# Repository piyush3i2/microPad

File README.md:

# RP2040 6-Key RGB Macro Pad

A compact RP2040-based macro pad with 6 keys, 4 SK6812 Mini RGB LEDs, and an SSD1306 OLED display.  
Built using MicroPython and KMK.

## Overview

This project is a custom USB macro pad.  
Each key sends a keyboard input, lights up an RGB LED, and the OLED shows basic status text.

---

## Hackpad

---

## Schematic

---

## PCB

---

## Case & Assembly

---

## Bill of Materials (BOM)

| Quantity | Component |
|--------:|-----------|
| 4 | SK6812 Mini RGB LED |
| 1 | MCP1700-330MB Voltage Regulator |
| 1 | MCP1700-500MB Voltage Regulator |
| 6 | MX-Style Mechanical Switch |
| 1 | XIAO-nRF52840-SMD |
| 1 | SSD1306 OLED Display |
| 2 | PinSocket 2.54mm 1x04 Vertical |
| 2 | PinHeader 2.54mm 1x02 Horizontal |

---

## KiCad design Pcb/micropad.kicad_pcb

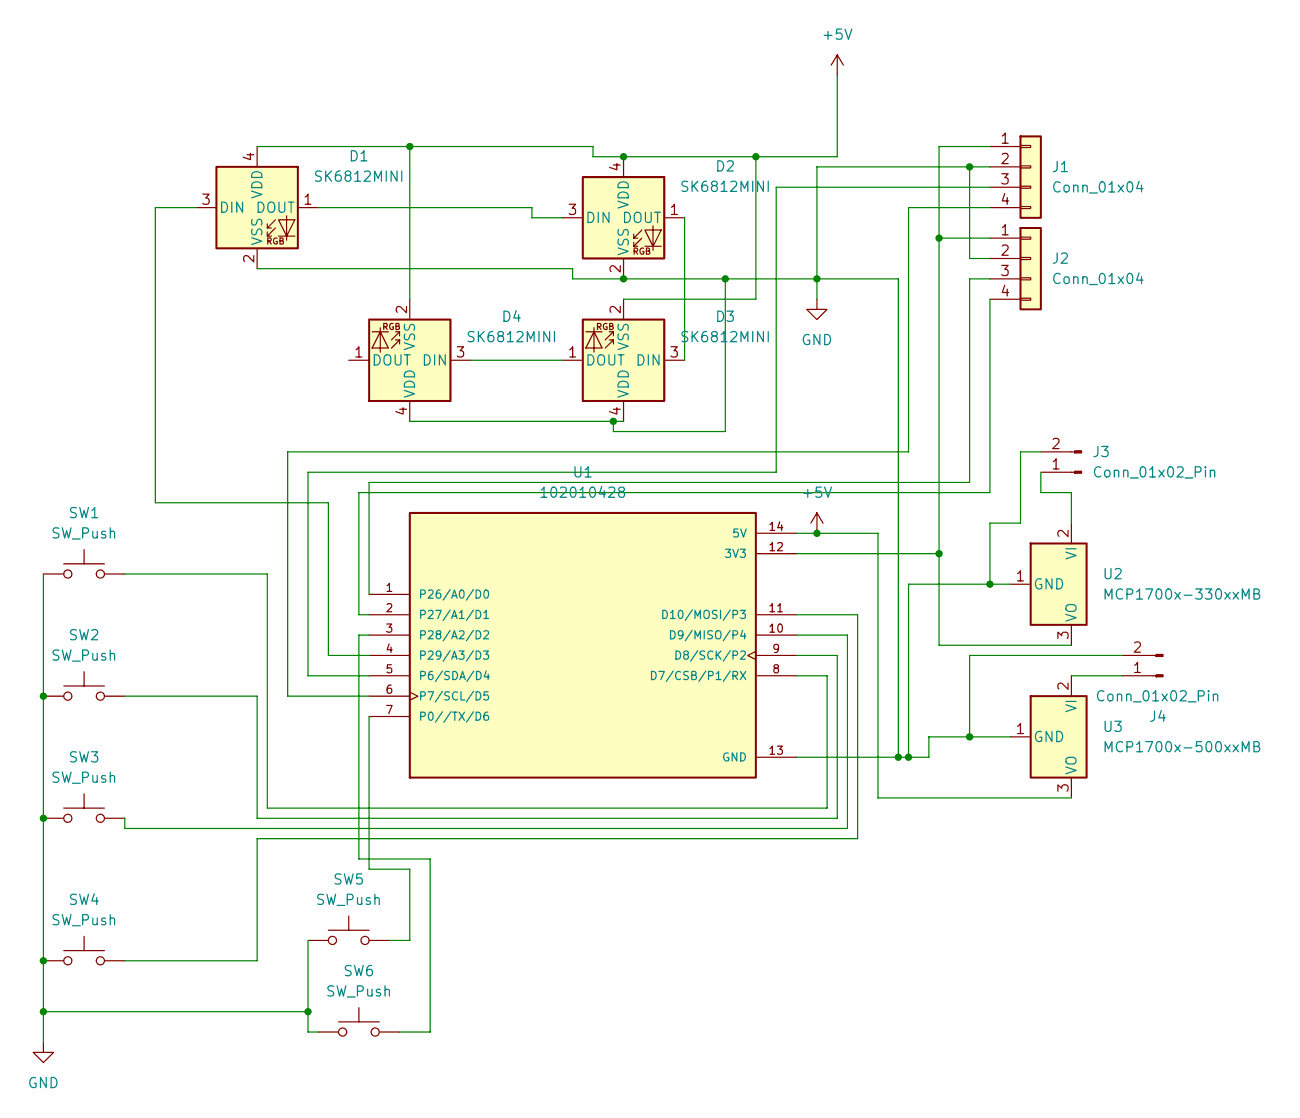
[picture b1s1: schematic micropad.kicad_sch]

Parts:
D1, D2, D3, D4: SK6812MINI; LED_SK6812MINI_PLCC4_3.5x3.5mm_P1.75mm
J1, J2: Conn_01x04; PinSocket_1x04_P2.54mm_Vertical
J3, J4: Conn_01x02_Pin; PinHeader_1x02_P2.54mm_Horizontal
SW1, SW2, SW3, SW4, SW5, SW6: SW_Push; SW_Cherry_MX_1.00u_PCB
U1: 102010428; MODULE_102010428; PARTREV 1.3; DigiKey_Part_Number 1597-102010428-ND
U2: MCP1700x-330xxMB; SOT-89-3
U3: MCP1700x-500xxMB; SOT-89-3

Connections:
+5V: D1.4 (VDD), D2.4 (VDD), D3.2 (VSS), D4.2 (VSS), U1.14 (5V), U3.3 (VO)
GND: D1.2 (VSS), D2.2 (VSS), D3.4 (VDD), D4.4 (VDD), J1.2, J2.2, J3.2, J4.2, SW1.1, SW2.1, SW3.1, SW4.1, SW5.1, SW6.1, U1.13 (GND), U2.1 (GND), U3.1 (GND)
unnamed: D1.3 (DIN), U1.4 (P29/A3/D3)
unnamed: D1.1 (DOUT), D2.3 (DIN)
unnamed: D2.1 (DOUT), D3.3 (DIN)
unnamed: D3.1 (DOUT), D4.3 (DIN)
unnamed: J1.1, J2.1, U1.12 (3V3), U2.3 (VO)
unnamed: J1.3, U1.5 (P6/SDA/D4)
unnamed: J1.4, U1.6 (P7/SCL/D5)
unnamed: J2.3, U1.1 (P26/A0/D0)
unnamed: J2.4, U1.2 (P27/A1/D1)
unnamed: J3.1, U2.2 (VI)
unnamed: J4.1, U3.2 (VI)
unnamed: SW1.2, U1.8 (D7/CSB/P1/RX)
unnamed: SW2.2, U1.9 (D8/SCK/P2)
unnamed: SW3.2, U1.10 (D9/MISO/P4)
unnamed: SW4.2, U1.11 (D10/MOSI/P3)
unnamed: SW5.2, U1.7 (P0//TX/D6)
unnamed: SW6.2, U1.3 (P28/A2/D2)

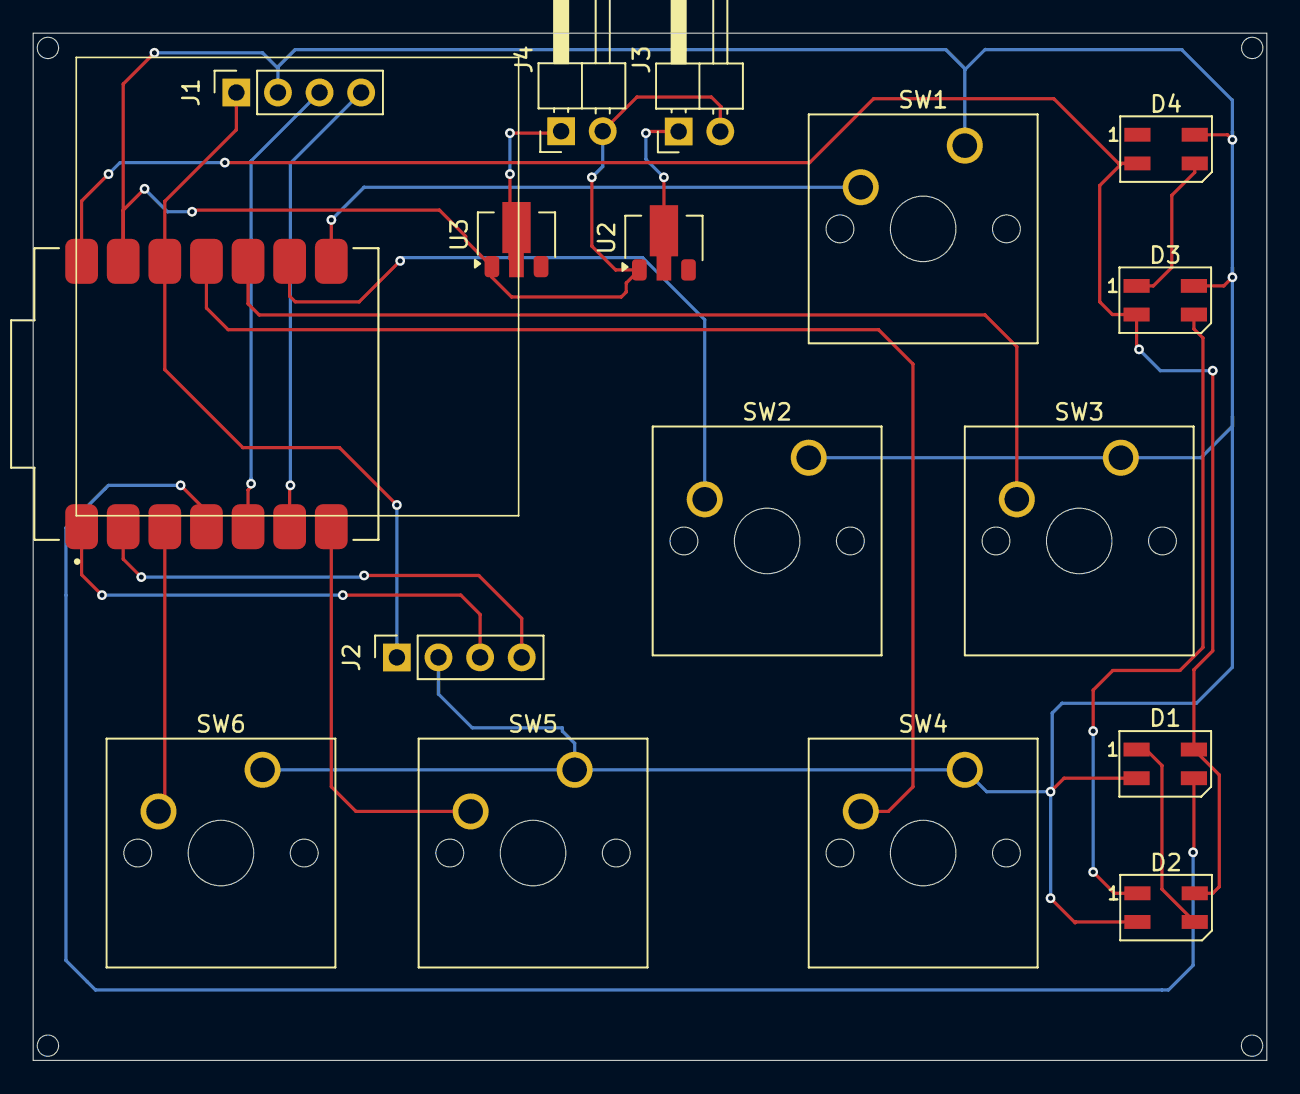
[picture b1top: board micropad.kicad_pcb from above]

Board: 2 copper layers, 75.3 x 62.7 mm, 17 parts (0 on the bottom side), 19 nets.

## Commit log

2025-12-29 Create bom
2025-12-29 Rename case with board.png to casewithboard.png
